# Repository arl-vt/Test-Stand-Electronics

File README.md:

# Test-Stand-Electronics
Includes PCB designs, Working code, Real time Stuff for Exoskeleton test Stand

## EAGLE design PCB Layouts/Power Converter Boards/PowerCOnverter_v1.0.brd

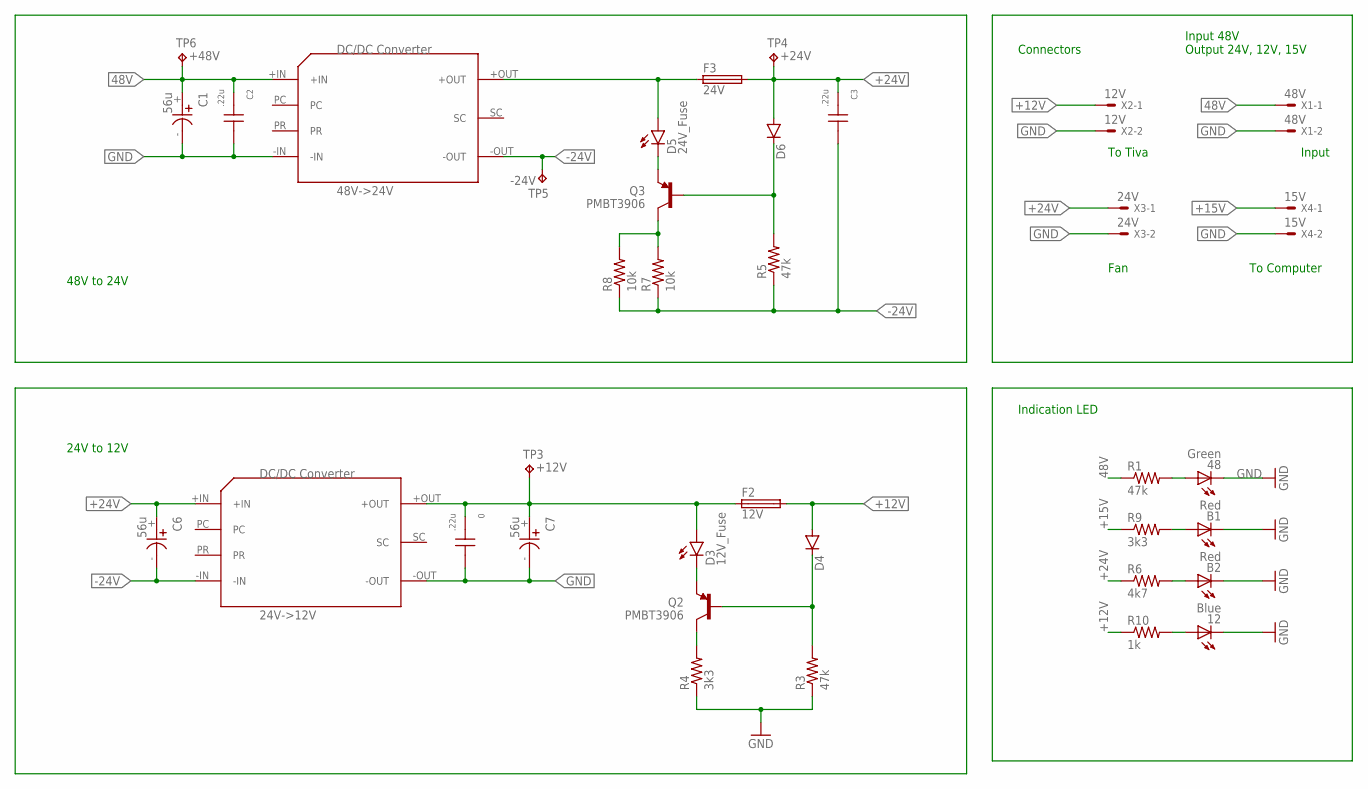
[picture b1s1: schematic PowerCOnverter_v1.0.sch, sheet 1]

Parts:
0: .22u; CERAMIC_CAP_5MM-LEAD
12: Blue; CHIPLED_1206
48: Green; CHIPLED_1206
B1, B2: Red; CHIPLED_1206
C1, C6, C7: 56u; CAP_5MM-LEAD-10MM-D
C2, C3: .22u; CERAMIC_CAP_5MM-LEAD
D3: 12V_Fuse; LED-0603
D4, D6: DIODESOD; SOD-323
D5: 24V_Fuse; LED-0603
F2: 12V; LITTELFUSE_NANO
F3: 24V; LITTELFUSE_NANO
PS1: 48V->24V; VICOR_MICRO_DC/DC_CONVERTER
PS2: 24V->12V; VICOR_MICRO_DC/DC_CONVERTER
Q2, Q3: PMBT3906; SOT23-3
R1: 47k; M1206
R3, R5: 47k; 0603-RES
R4: 3k3; 0603-RES
R6: 4k7; M1206
R7, R8: 10k; 0603-RES
R9: 3k3; M1206
R10: 1k; M1206
TP3: +12V; 5000_SERIES_TESTPOINT
TP4: +24V; 5000_SERIES_TESTPOINT
TP5: -24V; 5000_SERIES_TESTPOINT
TP6: +48V; 5000_SERIES_TESTPOINT
X1: 48V; 5566-2
X2: 12V; 5566-2
X3: 24V; 5566-2
X4: 15V; 5566-2

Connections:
48V: C1.+, C2.1, PS1.+IN, R1.1, TP6.P$1, X1.1
+12V: D4.A, F2.2, R10.1, X2.1
+15V: R9.1, X4.1; also elsewhere on the board
+24V: C3.1, C6.+, D6.A, F3.2, PS2.+IN, R6.1, TP4.P$1, X3.1; also elsewhere on the board
-24V: C3.2, C6.-, PS1.-OUT, PS2.-IN, R5.1, R7.1, R8.1, TP5.P$1; also elsewhere on the board
GND: 0.2, 12.C, 48.C, B1.C, B2.C, C1.-, C2.2, C7.-, PS1.-IN, PS2.-OUT, R3.1, R4.1, X1.2, X2.2, X3.2, X4.2; also elsewhere on the board
unnamed: D5.C, Q3.2 (E)
unnamed: D5.A, F3.1, PS1.+OUT
unnamed: Q3.3 (C), R7.2, R8.2
unnamed: 48.A, R1.2
unnamed: 0.1, C7.+, D3.A, F2.1, PS2.+OUT, TP3.P$1
unnamed: D3.C, Q2.2 (E)
unnamed: Q2.3 (C), R4.2
unnamed: D4.C, Q2.1 (B), R3.2
unnamed: D6.C, Q3.1 (B), R5.2
unnamed: B1.A, R9.2
unnamed: B2.A, R6.2
unnamed: 12.A, R10.2

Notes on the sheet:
48V to 24V
24V to 12V
Input 48V Output 24V, 12V, 15V
Connectors
Indication LED
Input
To Tiva
Fan
To Computer

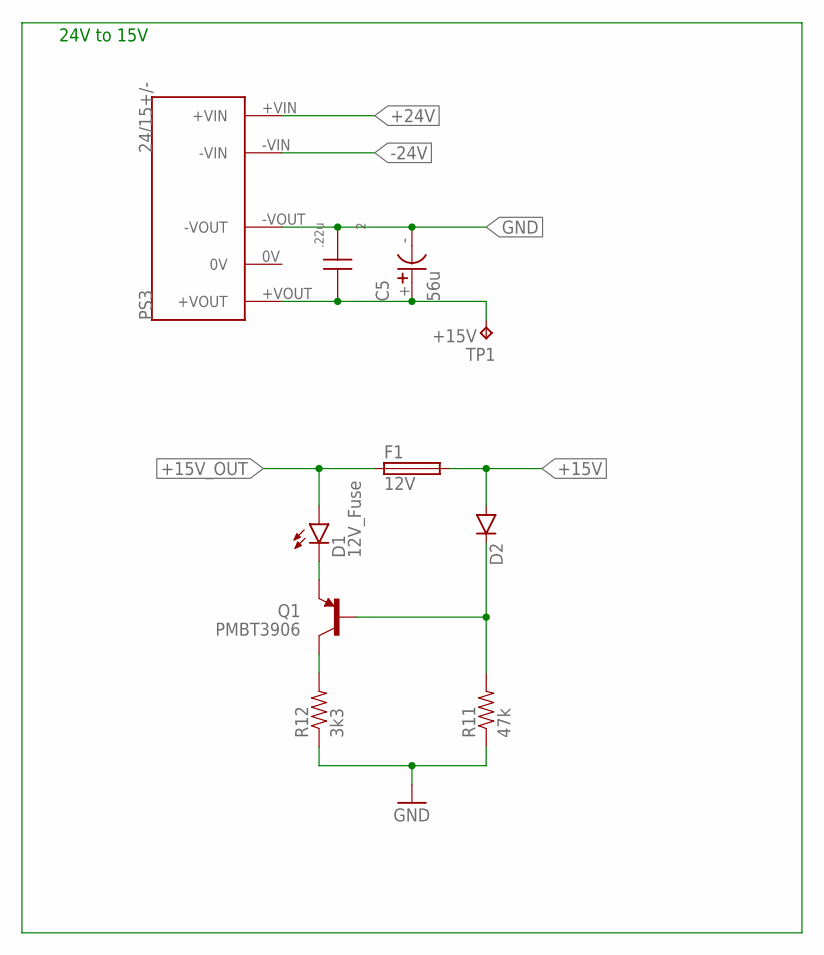
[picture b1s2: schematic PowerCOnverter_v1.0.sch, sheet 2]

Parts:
2: .22u; CERAMIC_CAP_5MM-LEAD
C5: 56u; CAP_5MM-LEAD-10MM-D
D1: 12V_Fuse; LED-0603
D2: DIODESOD; SOD-323
F1: 12V; LITTELFUSE_NANO
PS3: 24/15+/-; MURATA_NMH
Q1: PMBT3906; SOT23-3
R11: 47k; 0603-RES
R12: 3k3; 0603-RES
TP1: +15V; 5000_SERIES_TESTPOINT

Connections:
+15V: D2.A, F1.2; also elsewhere on the board
+15V_OUT: 2.2, C5.+, D1.A, F1.1, PS3.+VOUT, TP1.P$1
+24V: PS3.+VIN; also elsewhere on the board
-24V: PS3.-VIN; also elsewhere on the board
GND: 2.1, C5.-, PS3.-VOUT, R11.1, R12.1; also elsewhere on the board
unnamed: D1.C, Q1.2 (E)
unnamed: Q1.3 (C), R12.2
unnamed: D2.C, Q1.1 (B), R11.2

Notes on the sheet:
24V to 15V

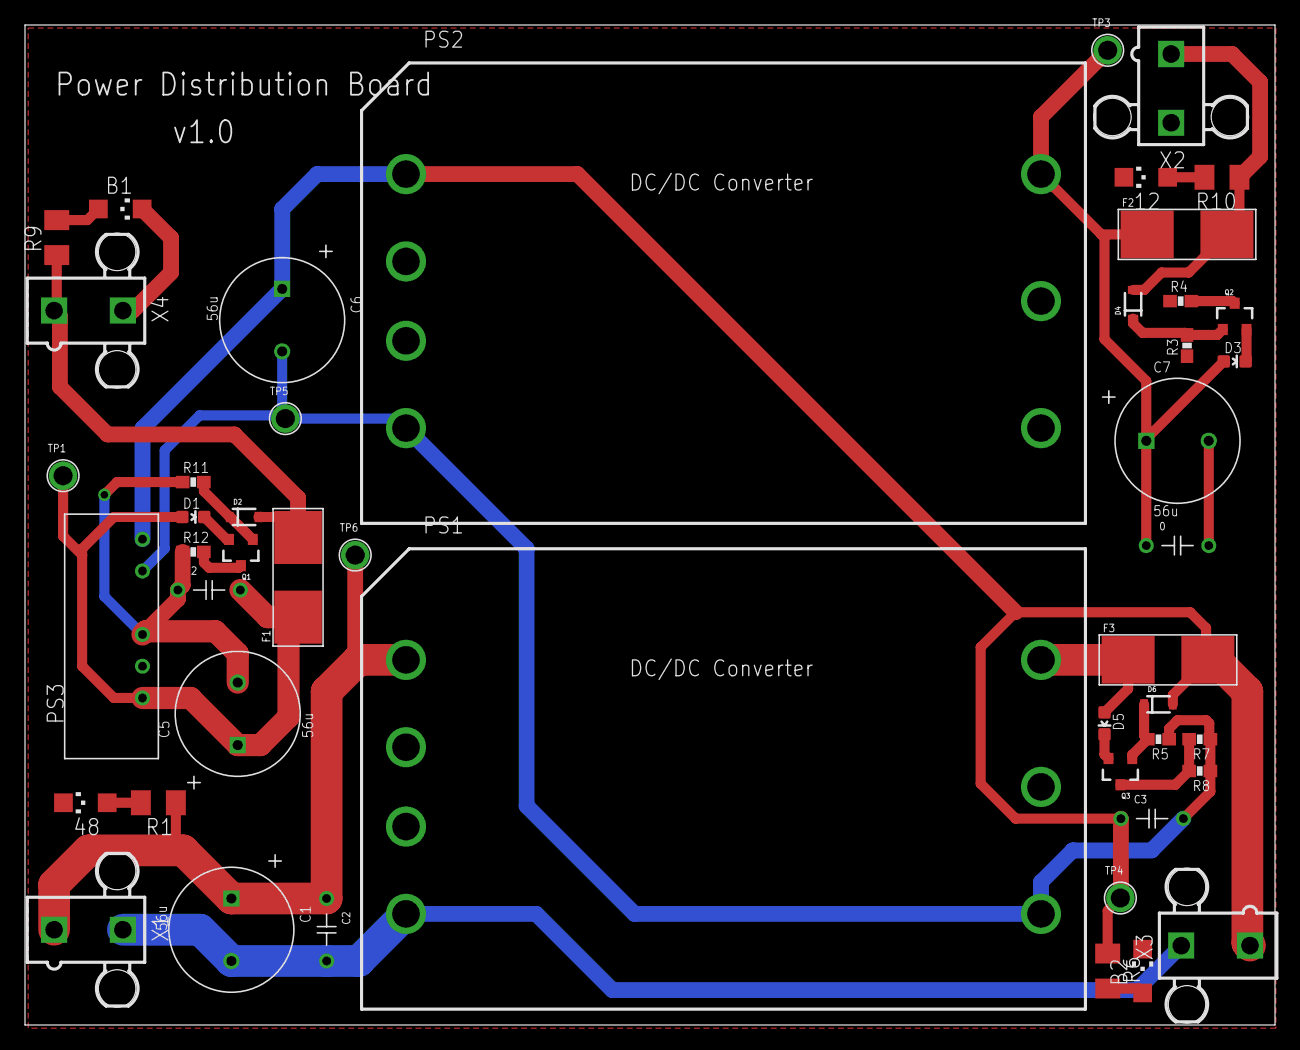
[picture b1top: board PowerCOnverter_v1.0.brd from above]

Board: 2 copper layers, 100.0 x 80.0 mm, 47 parts (0 on the bottom side), 22 nets.

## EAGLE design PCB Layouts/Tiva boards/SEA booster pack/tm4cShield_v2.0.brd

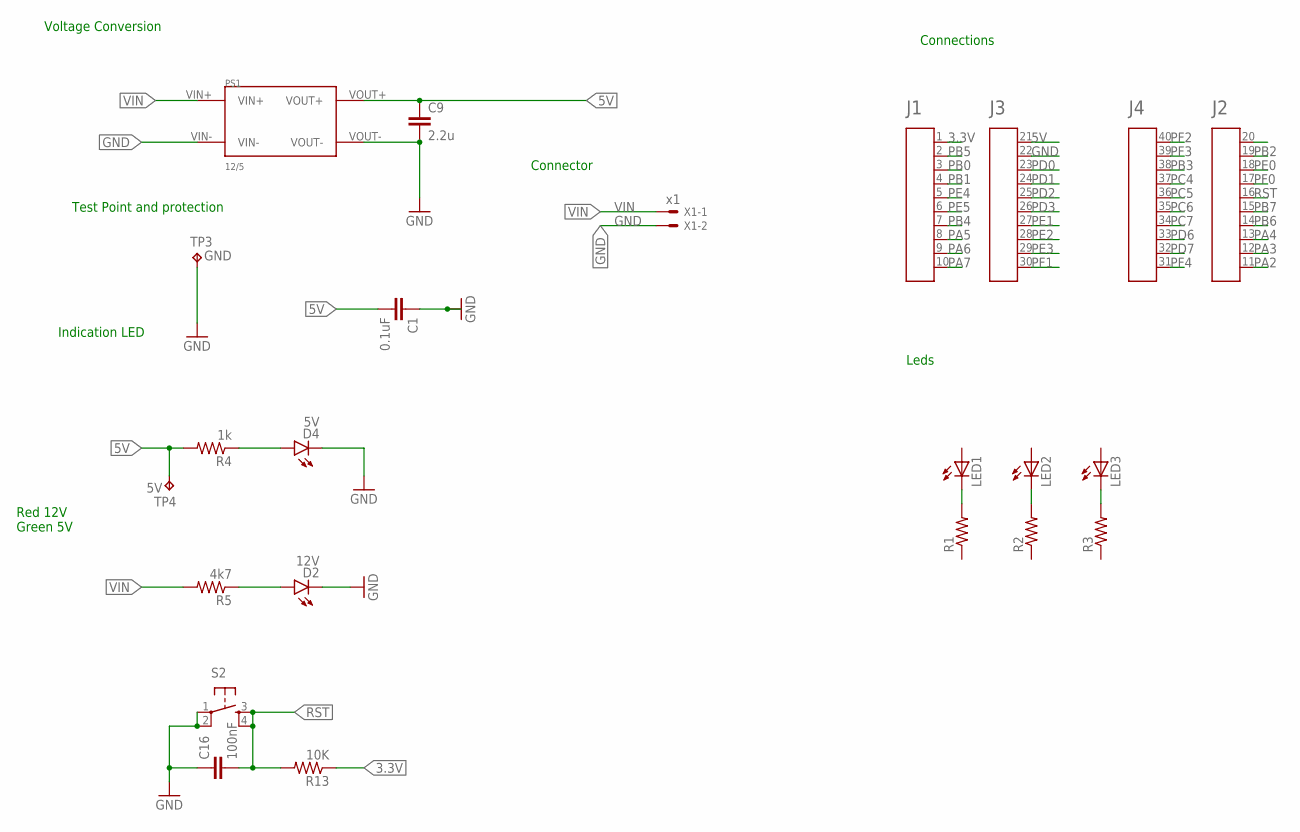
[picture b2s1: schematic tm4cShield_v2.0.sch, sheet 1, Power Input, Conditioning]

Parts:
A1: HEADER4X10-BOOSTERPACK; 4X10-BOOSTERPACK
C1: 0.1uF; 0603
C9: 2.2u; 0603-CAP
C16: 100nF; 0603-CAP; PARTNO C1608X7R1E104K
D2: 12V; LED-0603
D4: 5V; LED-0603
LED1, LED2, LED3: LED0603; LED-0603
PS1: 12/5; MURATA_NMG
R1, R2, R3: RESISTOR_0603; RESC0603
R4: 1k; 0603-RES
R5: 4k7; 0603-RES
R13: 10K; 0603-RES; PARTNO ERJ-3EKF1002V
S2: TAC_SWITCHPTH; TACTILE-PTH; PARTNO B3F-1005
TP3: GND; 5000_SERIES_TESTPOINT
TP4: 5V; 5000_SERIES_TESTPOINT
X1: x1; 53261-02

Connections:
3.3V: A1.1, R13.1; also elsewhere on the board
5V: A1.21, C1.2, C9.1, PS1.VOUT+, R4.2, TP4.P$1; also elsewhere on the board
GND: A1.22, C1.1, C9.2, C16.1, D2.C, D4.C, PS1.VIN-, PS1.VOUT-, S2.1, S2.2, TP3.P$1, X1.2; also elsewhere on the board
unnamed: D4.A, R4.1
unnamed: LED1.C, R1.2
unnamed: LED2.C, R2.2
unnamed: LED3.C, R3.2
unnamed: D2.A, R5.1
PA2: A1.11; also elsewhere on the board
PA3: A1.12
PA4: A1.13; also elsewhere on the board
PA5: A1.8
PA6: A1.9
PA7: A1.10
PB0: A1.3
PB1: A1.4
PB2: A1.19
PB3: A1.38
PB4: A1.7; also elsewhere on the board
PB5: A1.2; also elsewhere on the board
PB6: A1.14
PB7: A1.15
PC4: A1.37; also elsewhere on the board
PC5: A1.36; also elsewhere on the board
PC6: A1.35; also elsewhere on the board
PC7: A1.34
PD0: A1.23
PD1: A1.24
PD2: A1.25
PD3: A1.26
PD6: A1.33
PD7: A1.32
PE0: A1.18; also elsewhere on the board
PE1: A1.27
PE2: A1.28; also elsewhere on the board
PE3: A1.29; also elsewhere on the board
PE4: A1.5
PE5: A1.6
PF0: A1.17
PF1: A1.30
PF2: A1.40
PF3: A1.39
PF4: A1.31
RST: A1.16, C16.2, R13.2, S2.3, S2.4
VIN: PS1.VIN+, R5.2, X1.1; also elsewhere on the board

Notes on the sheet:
Voltage Conversion
Indication LED
Connector
Test Point and protection
Red 12V Green 5V
Connections
Leds

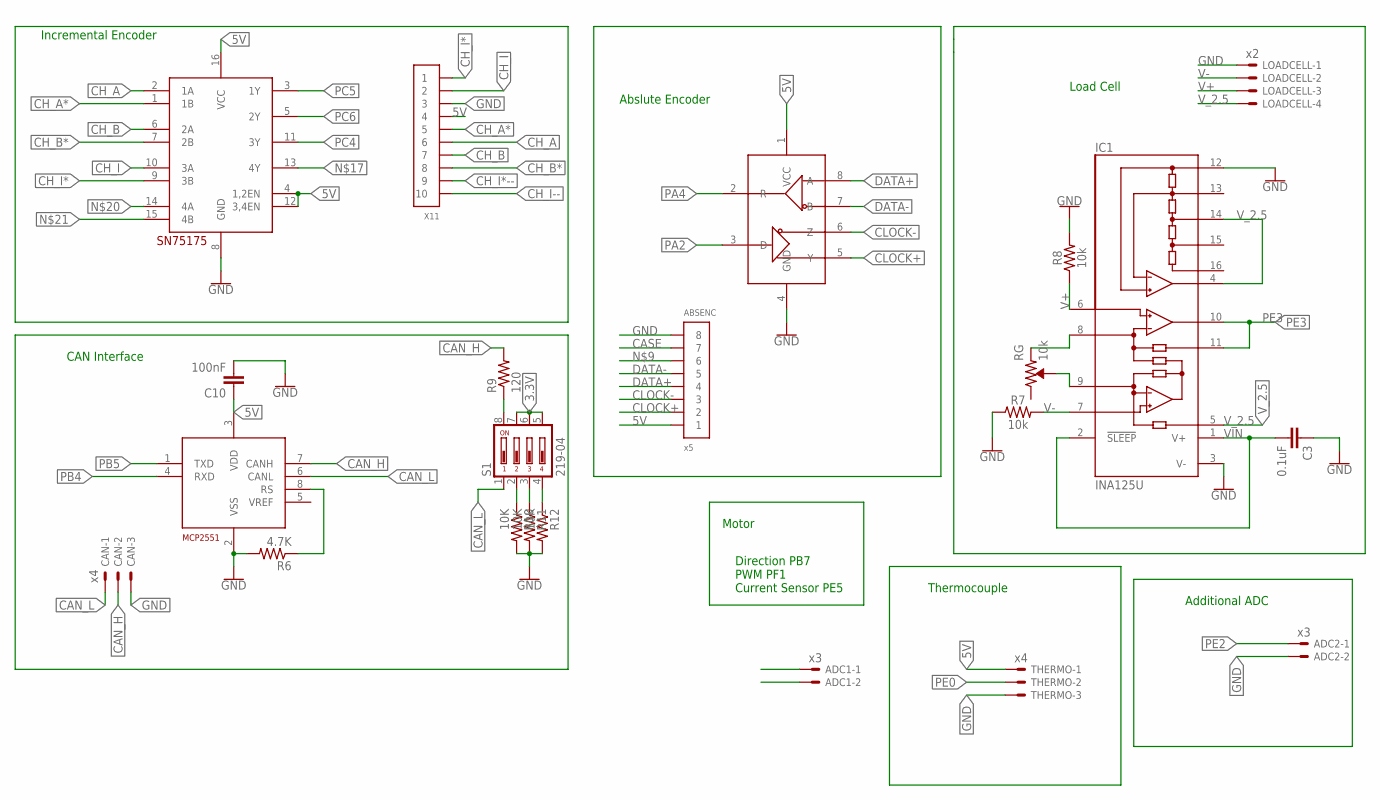
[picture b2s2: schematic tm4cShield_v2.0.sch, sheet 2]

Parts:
ABSENC: x5; PB-53261-08; PARTNO 0532610871
ADC1, ADC2: x3; 53261-02
C3: 0.1uF; 0603
C10: 100nF; 0603-CAP; PARTNO C1608X7R1E104K
CAN: x4; 53261-03
IC1: INA125U; SO16-1
LOADCELL: x2; 53261-04
R6: 4.7K; 0603-RES; PARTNO ERJ-3EKF4701V
R7, R8: 10k; 0603
R9: 120; 0603-RES; PARTNO ERJ-3GEYJ121V
R10, R11, R12: 10K; 0603-RES; PARTNO ERJ-3EKF1002V
RG: 10k; TRIMPOT-PTH-3386U
S1: 219-04; CTS-219-04; PARTNO 219-4LPST; DIGIKEY CT2194LPST-ND
THERMO: x4; 53261-03
U2: MCP2551; SOIC8; PARTNO MCP2551-I/SN
U$2: SN75175; SOIC16; PARTNO SN75175DR
U$4: SP490; SOIC8; PARTNO SP490CN-L
X11: CONN_10-1-53261; PB-53261-10; PARTNO 0532611071

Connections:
3.3V: S1.5, S1.6, S1.7; also elsewhere on the board
5V: ABSENC.1, C10.1, THERMO.1, U2.3 (VDD), U$2.4 (1,2EN), U$2.12 (3,4EN), U$2.16 (VCC), U$4.1 (VCC), X11.4; also elsewhere on the board
CAN_H: CAN.2, R9.2, U2.7 (CANH)
CAN_L: CAN.1, S1.1, U2.6 (CANL)
CASE: ABSENC.7
CH_A: U$2.2 (1A), X11.6
CH_A*: U$2.1 (1B), X11.5
CH_B: U$2.6 (2A), X11.7
CH_B*: U$2.7 (2B), X11.8
CH_I: U$2.10 (3A), X11.2
CH_I*: U$2.9 (3B), X11.1
CH_I*--: X11.9
CH_I--: X11.10
CLOCK+: ABSENC.2, U$4.5 (Y)
CLOCK-: ABSENC.3, U$4.6 (Z)
DATA+: ABSENC.4, U$4.8 (A)
DATA-: ABSENC.5, U$4.7 (B)
GND: ABSENC.8, ADC2.2, C3.1, C10.2, CAN.3, IC1.3 (V-), IC1.12 (REFCOM), LOADCELL.1, R6.2, R7.1, R8.2, R10.2, R11.2, R12.2, THERMO.3, U2.2 (VSS), U$2.8 (GND), U$4.4 (GND), X11.3; also elsewhere on the board
unnamed: IC1.8 (RG), RG.1 (CCW)
unnamed: IC1.9 (RG), RG.2 (WIPER)
unnamed: R9.1, S1.8
unnamed: R6.1, U2.8 (RS)
unnamed: R10.1, S1.2
unnamed: R11.1, S1.3
unnamed: R12.1, S1.4
PA2: U$4.3 (D); also elsewhere on the board
PA4: U$4.2 (R); also elsewhere on the board
PB4: U2.4 (RXD); also elsewhere on the board
PB5: U2.1 (TXD); also elsewhere on the board
PC4: U$2.11 (3Y); also elsewhere on the board
PC5: U$2.3 (1Y); also elsewhere on the board
PC6: U$2.5 (2Y); also elsewhere on the board
PE0: THERMO.2; also elsewhere on the board
PE2: ADC2.1; also elsewhere on the board
PE3: IC1.10 (OUT), IC1.11 (SENSE); also elsewhere on the board
V+: IC1.6 (+IN), LOADCELL.3, R8.1
V-: IC1.7 (-IN), LOADCELL.2, R7.2
VIN: C3.2, IC1.1 (V+), IC1.2 (!SLEEP); also elsewhere on the board
V_2.5: IC1.4 (REFOUT), IC1.5 (REF), IC1.14 (REF2.5), LOADCELL.4

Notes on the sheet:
Motor
Direction PB7 PWM PF1 Current Sensor PE5
Additional ADC
Thermocouple
Abslute Encoder
Load Cell
Incremental Encoder
CAN Interface

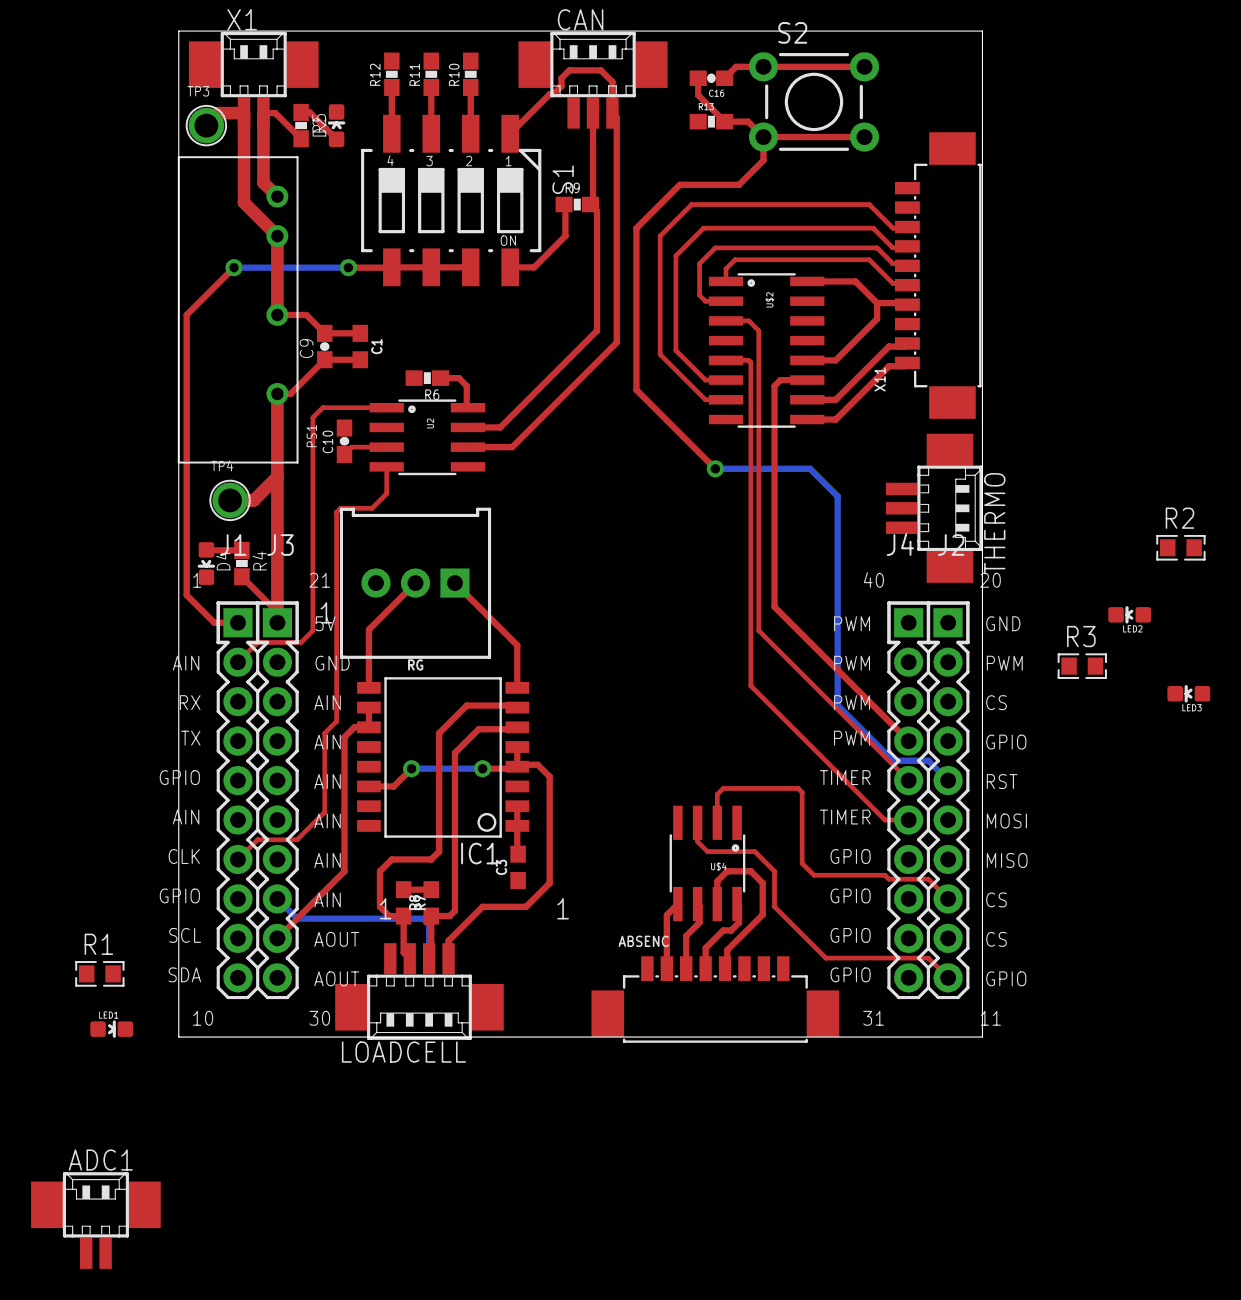
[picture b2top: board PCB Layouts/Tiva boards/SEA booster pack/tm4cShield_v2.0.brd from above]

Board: 2 copper layers, 51.7 x 64.8 mm, 42 parts (1 on the bottom side), 42 nets.

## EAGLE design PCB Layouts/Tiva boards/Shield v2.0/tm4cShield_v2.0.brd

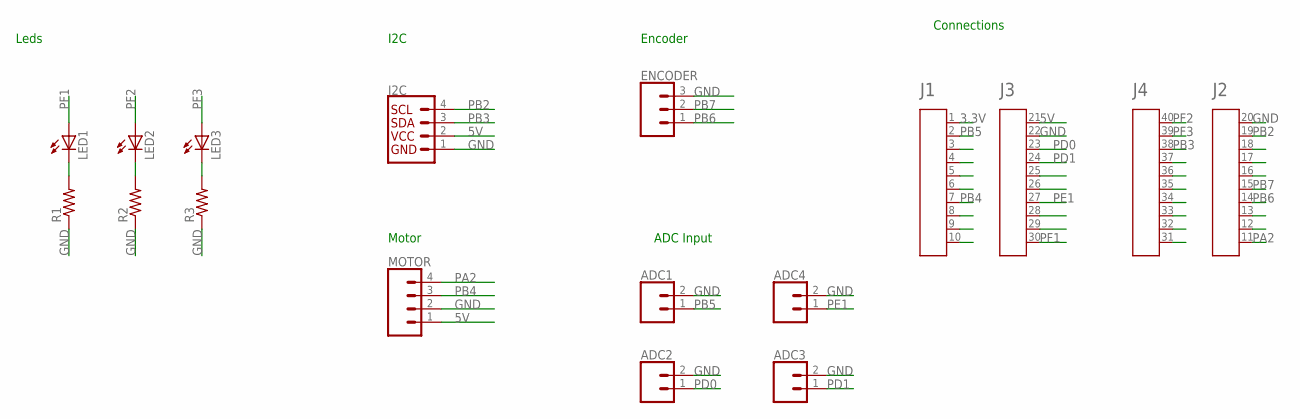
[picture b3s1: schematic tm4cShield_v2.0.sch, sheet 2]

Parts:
A1: HEADER4X10-BOOSTERPACK; 4X10-BOOSTERPACK
ADC1, ADC2, ADC3, ADC4: CONN_02; 1X02
ENCODER: CONN_03JST-PTH-VERT; JST-3-PTH-VERT
I2C: I2C_STANDARD; 1X04
LED1, LED2, LED3: LED0603; LED-0603
MOTOR: CONN_04JST-PTH-VERT; JST-4-PTH-VERT
R1, R2, R3: RESISTOR_0603; RESC0603

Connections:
3.3V: A1.1
5V: A1.21, I2C.2, MOTOR.1
GND: A1.20, A1.22, ADC1.2, ADC2.2, ADC3.2, ADC4.2, ENCODER.3, I2C.1, MOTOR.2, R1.1, R2.1, R3.1
unnamed: LED1.C, R1.2
unnamed: LED2.C, R2.2
unnamed: LED3.C, R3.2
PA2: A1.11, MOTOR.4
PB2: A1.19, I2C.4
PB3: A1.38, I2C.3
PB4: A1.7, MOTOR.3
PB5: A1.2, ADC1.1
PB6: A1.14, ENCODER.1
PB7: A1.15, ENCODER.2
PD0: A1.23, ADC2.1
PD1: A1.24, ADC3.1
PE1: A1.27, ADC4.1
PF1: A1.30, LED1.A
PF2: A1.40, LED2.A
PF3: A1.39, LED3.A

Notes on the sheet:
Leds
Connections
I2C
Encoder
Motor
ADC Input

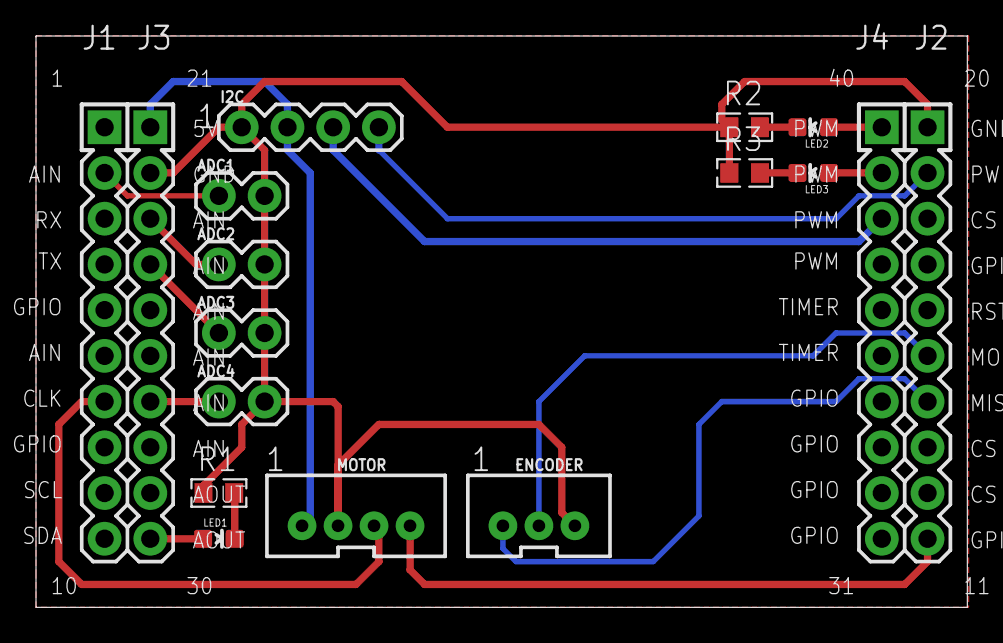
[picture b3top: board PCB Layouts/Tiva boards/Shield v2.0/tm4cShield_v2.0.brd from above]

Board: 2 copper layers, 51.7 x 31.7 mm, 14 parts (0 on the bottom side), 18 nets.

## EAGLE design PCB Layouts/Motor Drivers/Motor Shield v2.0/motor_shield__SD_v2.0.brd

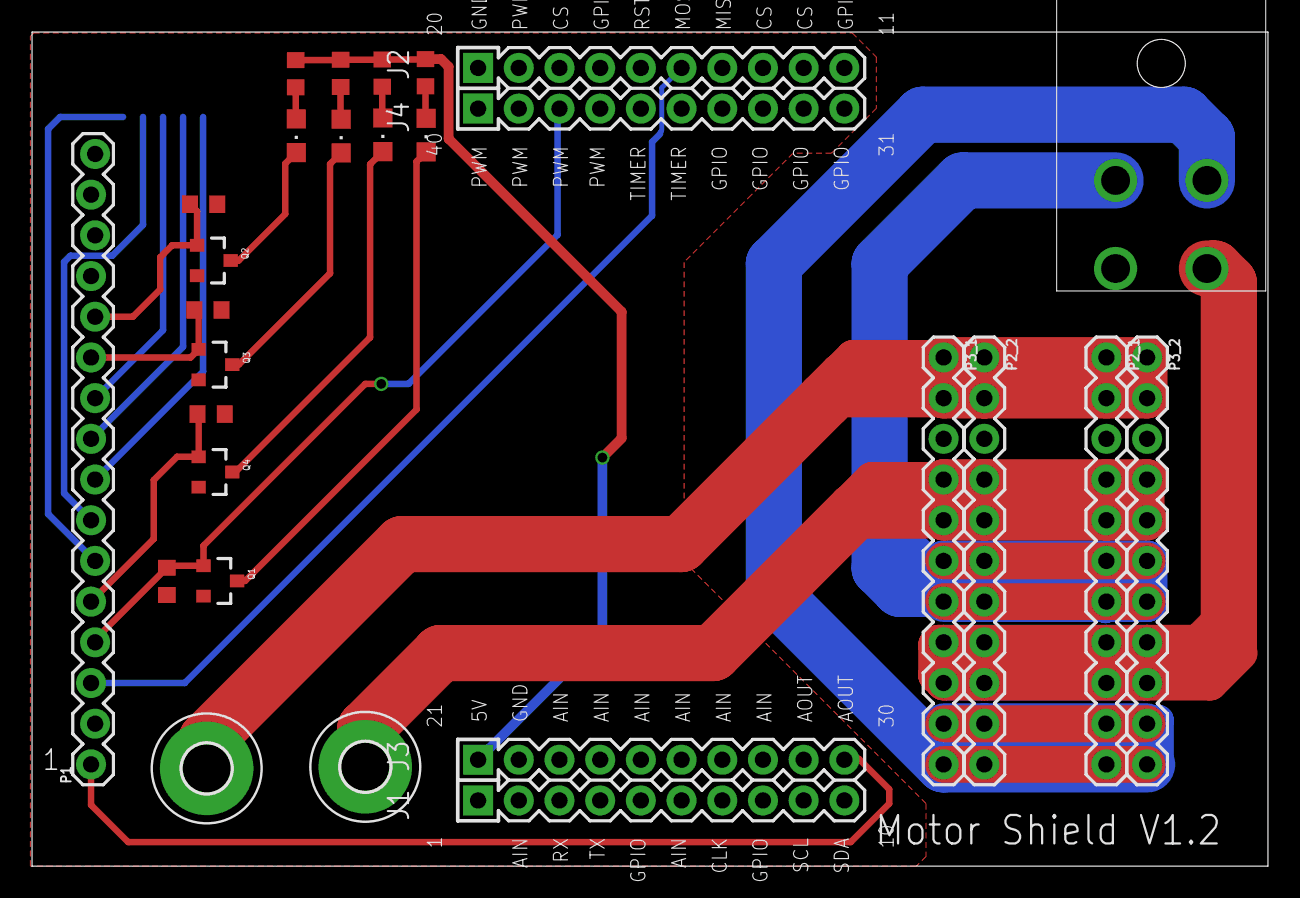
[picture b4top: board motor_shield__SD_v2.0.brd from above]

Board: 2 copper layers, 77.1 x 52.1 mm, 26 parts (1 on the bottom side), 26 nets.

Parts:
A1: 4X10-BOOSTERPACK
C1: MOLEX4CON
H1, H3: MOUNT-PAD-ROUND3.0; 3,0-PAD
LED1, LED2, LED3, LED4: CHIPLED_0805
P1: 1X16_LOCK
P2_1, P2_2, P3_1, P3_2: 1X11
Q1, Q2, Q3, Q4: MMBT2222A; SOT23-3
R1, R2, R3, R4: 220; R0603
R5, R6, R7, R8: 1000; R0603
X1: PB-53261-05

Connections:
*INHIBIT: P1.5, Q4.1, R7.2
+5V: A1.21, R1.2, R2.2, R3.2, R4.2
CURRENT_MONITOR: A1.38, P1.4, Q1.1, R5.2
CURRENT_REF: P1.11, Q3.1, R8.2
DIRECTION: A1.15, P1.3
FAULT_OUT: P1.12, Q2.1, R6.2
GND: A1.22, P1.2, Q1.2, Q2.2, Q3.2, Q4.2, R5.1, R6.1, R7.1, R8.1
GND_HALL: P1.7, X1.2
HALL1: P1.8, X1.5
HALL2: P1.9, X1.4
HALL3: P1.10, X1.3
HIGH_VOL: H3.B3,0, P2_1.1, P2_1.2, P2_2.1, P2_2.2, P3_1.1, P3_1.2, P3_2.1, P3_2.2
MOTOR_A: C1.2, P2_1.10, P2_1.11, P2_2.10, P2_2.11, P3_1.10, P3_1.11, P3_2.10, P3_2.11
MOTOR_B: C1.1, P2_1.8, P2_1.9, P2_2.8, P2_2.9, P3_1.8, P3_1.9, P3_2.8, P3_2.9
MOTOR_C: C1.4, P2_1.6, P2_1.7, P2_2.6, P2_2.7, P3_1.6, P3_1.7, P3_2.6, P3_2.7
unnamed: LED1.A, R1.1
unnamed: LED2.A, R2.1
unnamed: LED3.A, R3.1
unnamed: LED4.A, R4.1
unnamed: LED1.C, Q1.3
unnamed: LED2.C, Q3.3
unnamed: LED3.C, Q2.3
unnamed: LED4.C, Q4.3
PWM: A1.30, P1.1
PWR_GND: H1.B3,0, P2_1.4, P2_1.5, P2_2.4, P2_2.5, P3_1.4, P3_1.5, P3_2.4, P3_2.5
V+_HALL: P1.6, X1.1

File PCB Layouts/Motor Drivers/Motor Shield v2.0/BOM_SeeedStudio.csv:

Part/Designator,DigiKey,Quantity,Description
C1,WM10392-ND,1,Molex Megafit
X1,WM7623CT-ND,1,PicoBlade 5 pos
LED1,475-1410-2-ND,1,Green
LED2,475-1278-2-ND,1,Red
LED3,475-2560-2-ND,1,Yellow
LED4,VAOL-S8SB4TR-ND,1,Blue
"R1, R2, R3, R4",311-220GRTR-ND,4,"220 ohm, 0603 Resistor"
"R5, R6, R7, R8",311-1.0KGRTR-ND,4,"1000 ohm, 0603 resistor"
"Q1, Q2, Q3, Q4",MMBT2222ALT1GOSTR-ND,4,NPN Transistor

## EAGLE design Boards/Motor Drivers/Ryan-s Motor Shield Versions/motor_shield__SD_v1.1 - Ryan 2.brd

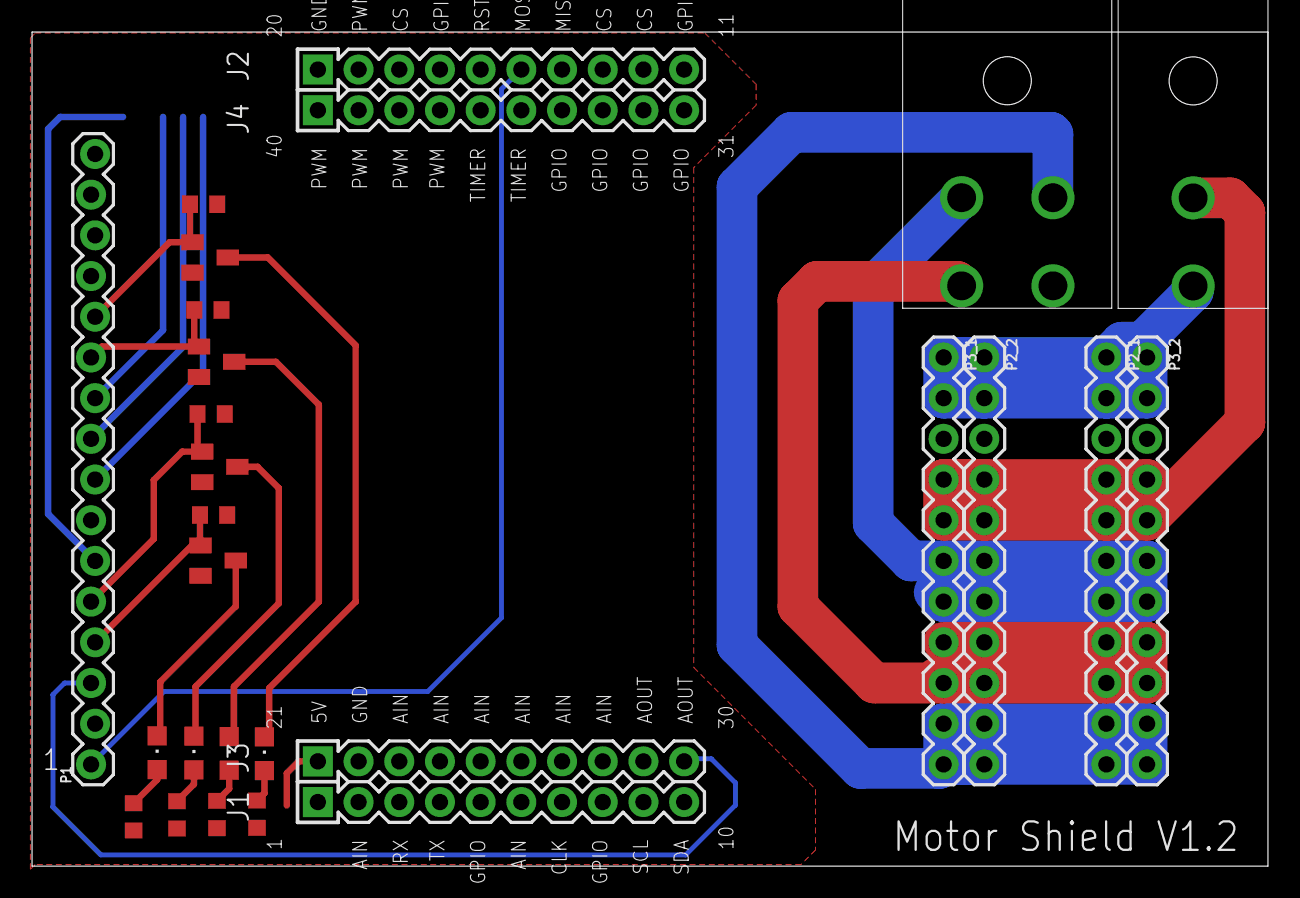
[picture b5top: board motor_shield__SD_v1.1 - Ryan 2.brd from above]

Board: 2 copper layers, 77.1 x 52.1 mm, 25 parts (1 on the bottom side), 25 nets.

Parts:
A1: 4X10-BOOSTERPACK
LED1, LED2, LED3, LED4: CHIPLED_0805
MN1, MN2, MN3, MN4: SOT23
P1: 1X16_LOCK
P2_1, P2_2, P3_1, P3_2: 1X11
R1, R2, R3, R4: 220; R0603
R5, R6, R7, R8: 1000; R0603
U$1: MOLEX2CON
U$2: MOLEX4CON
X1: PB-53261-05

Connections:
*INHIBIT: MN4.1, P1.5, R7.2
+5V: A1.21, R1.2, R2.2, R3.2, R4.2
CURRENT_MONITOR: MN1.1, P1.4, R5.2
CURRENT_REF: MN2.1, P1.11, R8.2
DIRECTION: A1.30, P1.3
FAULT_OUT: MN3.1, P1.12, R6.2
GND: A1.22, MN1.2, MN2.2, MN3.2, MN4.2, P1.2, R5.1, R6.1, R7.1, R8.1, X1.2
HALL1: P1.8, X1.5
HALL2: P1.9, X1.4
HALL3: P1.10, X1.3
HIGH_VOL: P2_1.1, P2_1.2, P2_2.1, P2_2.2, P3_1.1, P3_1.2, P3_2.1, P3_2.2, U$1.1
MOTOR_A: P2_1.10, P2_1.11, P2_2.10, P2_2.11, P3_1.10, P3_1.11, P3_2.10, P3_2.11, U$2.2
MOTOR_B: P2_1.8, P2_1.9, P2_2.8, P2_2.9, P3_1.8, P3_1.9, P3_2.8, P3_2.9, U$2.3
MOTOR_C: P2_1.6, P2_1.7, P2_2.6, P2_2.7, P3_1.6, P3_1.7, P3_2.6, P3_2.7, U$2.4
unnamed: LED1.A, R1.1
unnamed: LED2.A, R2.1
unnamed: LED3.A, R3.1
unnamed: LED4.A, R4.1
unnamed: LED1.C, MN1.3
unnamed: LED2.C, MN2.3
unnamed: LED3.C, MN3.3
unnamed: LED4.C, MN4.3
PWM: A1.15, P1.1
PWR_GND: P2_1.4, P2_1.5, P2_2.4, P2_2.5, P3_1.4, P3_1.5, P3_2.4, P3_2.5, U$1.2
V+_HALL: P1.6, X1.1

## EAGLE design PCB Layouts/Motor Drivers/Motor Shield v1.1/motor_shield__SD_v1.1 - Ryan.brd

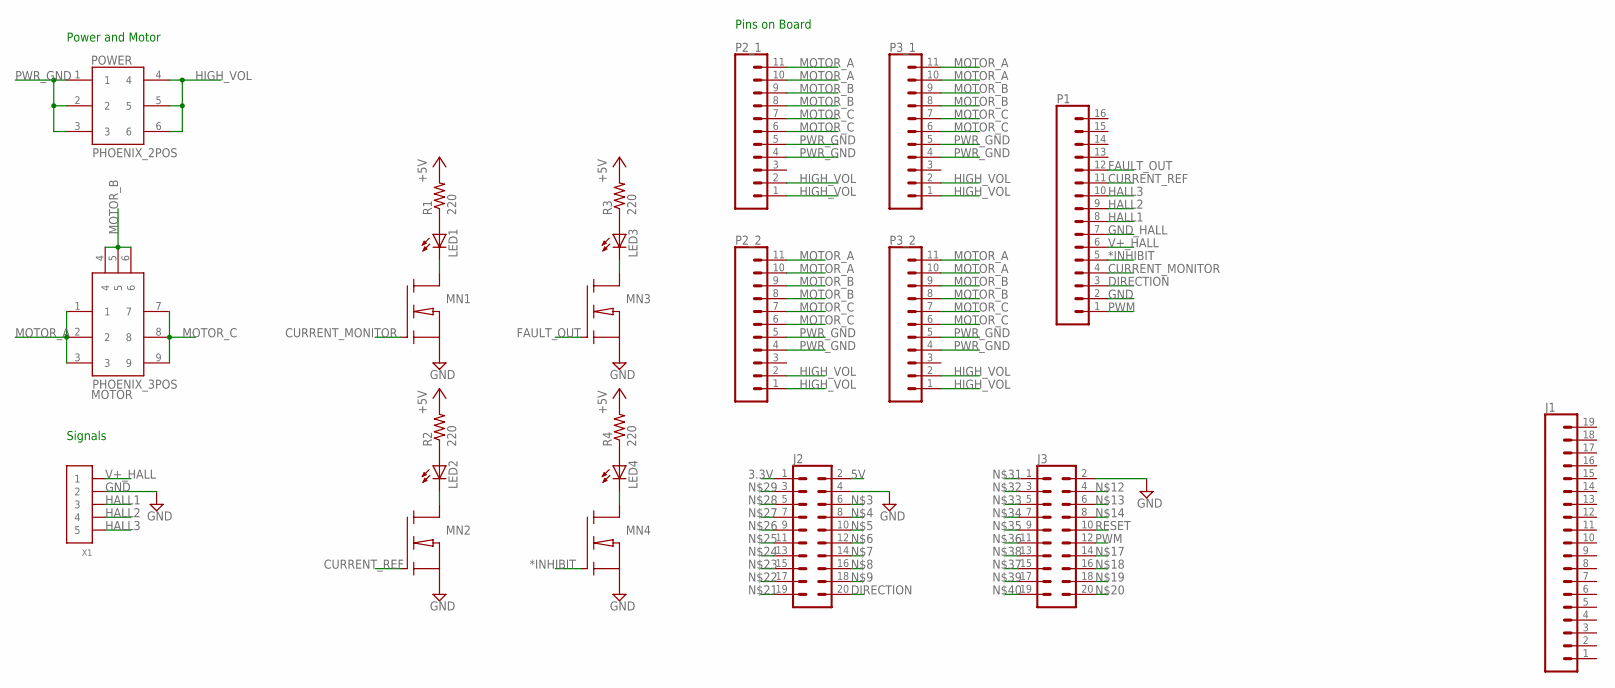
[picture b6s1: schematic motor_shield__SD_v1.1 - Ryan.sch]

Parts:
J1: CONN_19; 1X19
J2, J3: CONN_10X2; 2X10
LED1, LED2, LED3, LED4: LEDCHIPLED_0805; CHIPLED_0805
MN1, MN2, MN3, MN4: NMOS; SOT23
MOTOR: PHOENIX_3POS
P1: CONN_16LOCK; 1X16_LOCK
P2_1, P2_2, P3_1, P3_2: CONN_11; 1X11
POWER: PHOENIX_2POS
R1, R2, R3, R4: 220; R0603
X1: CONN_5-1-53261; PB-53261-05

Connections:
3.3V: J2.1
5V: J2.2
*INHIBIT: MN4.1 (G), P1.5
+5V: R1.2, R2.2, R3.2, R4.2
CURRENT_MONITOR: MN1.1 (G), P1.4
CURRENT_REF: MN2.1 (G), P1.11
DIRECTION: J2.20, P1.3
FAULT_OUT: MN3.1 (G), P1.12
GND: J2.4, J3.2, MN1.2 (S), MN2.2 (S), MN3.2 (S), MN4.2 (S), P1.2, X1.2
GND_HALL: P1.7
HALL1: P1.8, X1.3
HALL2: P1.9, X1.4
HALL3: P1.10, X1.5
HIGH_VOL: P2_1.1, P2_1.2, P2_2.1, P2_2.2, P3_1.1, P3_1.2, P3_2.1, P3_2.2, POWER.4, POWER.5, POWER.6
MOTOR_A: MOTOR.1, MOTOR.2, MOTOR.3, P2_1.10, P2_1.11, P2_2.10, P2_2.11, P3_1.10, P3_1.11, P3_2.10, P3_2.11
MOTOR_B: MOTOR.4, MOTOR.5, MOTOR.6, P2_1.8, P2_1.9, P2_2.8, P2_2.9, P3_1.8, P3_1.9, P3_2.8, P3_2.9
MOTOR_C: MOTOR.7, MOTOR.8, MOTOR.9, P2_1.6, P2_1.7, P2_2.6, P2_2.7, P3_1.6, P3_1.7, P3_2.6, P3_2.7
unnamed: LED1.A, R1.1
unnamed: LED2.A, R2.1
unnamed: LED3.A, R3.1
unnamed: LED4.A, R4.1
unnamed: LED1.C, MN1.3 (D)
unnamed: LED2.C, MN2.3 (D)
unnamed: LED3.C, MN3.3 (D)
unnamed: LED4.C, MN4.3 (D)
PWM: J3.12, P1.1
PWR_GND: P2_1.4, P2_1.5, P2_2.4, P2_2.5, P3_1.4, P3_1.5, P3_2.4, P3_2.5, POWER.1, POWER.2, POWER.3
RESET: J3.10
V+_HALL: P1.6, X1.1

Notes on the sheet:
Power and Motor
Signals
Pins on Board

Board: 2 copper layers, 23 parts (1 on the bottom side), 25 nets, no tracks yet.

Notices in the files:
parts and their libraries:
SparkFun-Connectors: Licensing: Creative Commons ShareAlike 4.0 International - https://creativecommons.org/licenses/by-sa/4.0
SparkFun-Electromechanical: Licensing: CC v3.0 Share-Alike You are welcome to use this library for commercial purposes.
